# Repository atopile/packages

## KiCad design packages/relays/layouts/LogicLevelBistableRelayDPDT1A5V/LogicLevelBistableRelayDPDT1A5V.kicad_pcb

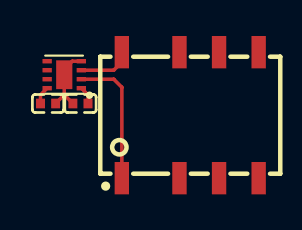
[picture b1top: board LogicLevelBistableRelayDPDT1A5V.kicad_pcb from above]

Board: 2 copper layers, 4 parts (0 on the bottom side), 5 nets.

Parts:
C1, C2: 0F; C0402
U1: WSON-8_L2.0-W2.0-P0.50-TL-EP
U2: RELAY-SMD_G6KU-2F-Y

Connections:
hv: C1.1, U1.8
lv: C1.2, C2.2, U1.4, U1.9
motor_outs[0]: U1.2, U2.1
motor_outs[1]: U1.3, U2.8
motor_power_decoupling_capacitor-power-hv: C2.1, U1.1

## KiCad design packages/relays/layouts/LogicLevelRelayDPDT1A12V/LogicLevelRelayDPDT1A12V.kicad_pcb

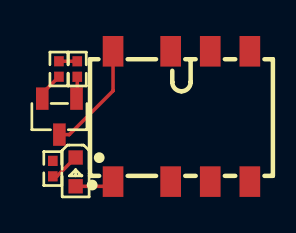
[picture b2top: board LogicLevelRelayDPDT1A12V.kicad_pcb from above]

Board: 2 copper layers, 6 parts (0 on the bottom side), 6 nets.

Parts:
K1: RELAY-SMD_G6K-2F-Y
LED1: LED0603-RD
Q1: SOT-23-3_L2.9-W1.3-P1.90-LS2.4-BR
R1, R2: 10000Ω; R0402
R3: 20000Ω; R0402

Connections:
anode: K1.1, LED1.2
cathode: LED1.1, R3.1
contacts[1]: K1.8, Q1.3
gate: Q1.1, R2.2
line: R1.1, R2.1
lv: Q1.2, R1.2, R3.2
